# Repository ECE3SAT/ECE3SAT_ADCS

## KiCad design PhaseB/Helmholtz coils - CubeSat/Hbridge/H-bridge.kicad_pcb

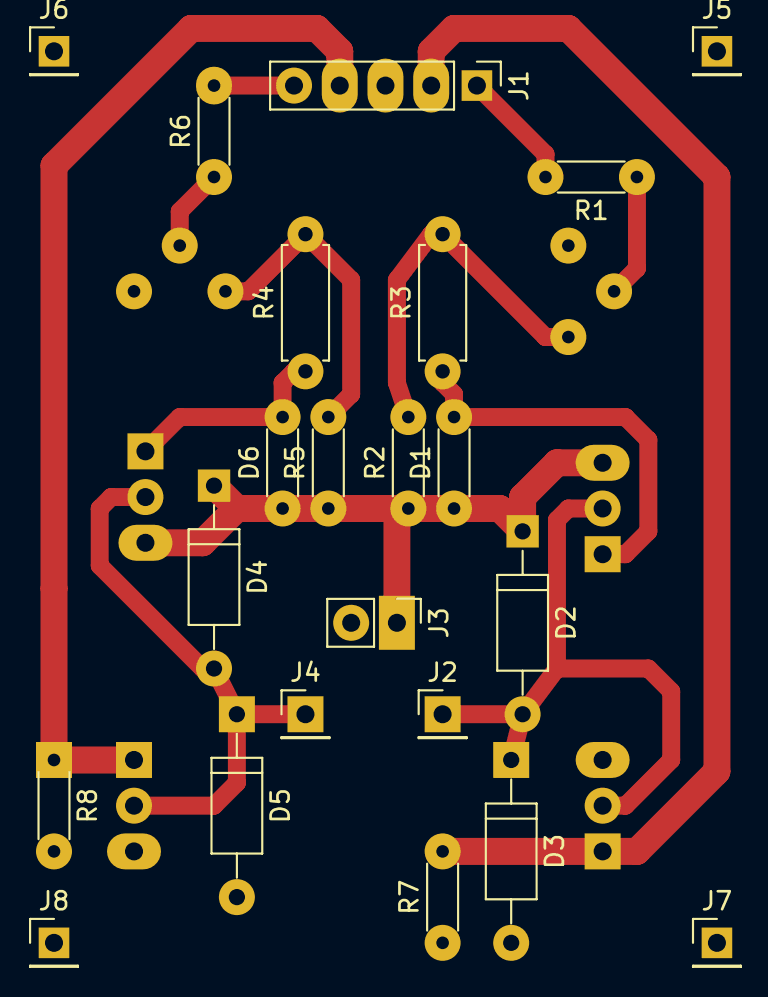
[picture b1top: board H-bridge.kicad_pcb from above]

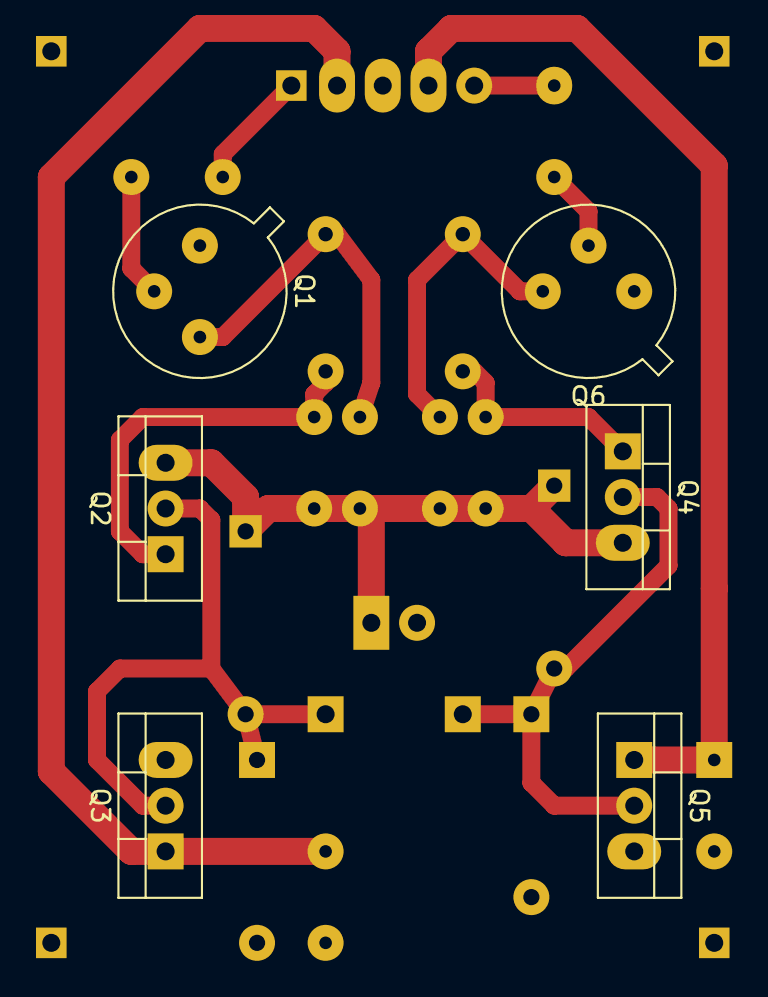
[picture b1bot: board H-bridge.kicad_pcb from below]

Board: 2 copper layers, 28 parts (6 on the bottom side), 14 nets.

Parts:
D1, D6: 10V; R_Axial_DIN0204_L3.6mm_D1.6mm_P5.08mm_Horizontal
D2, D3, D4, D5: 1N4007; D_A-405_P10.16mm_Horizontal
J1: Conn_01x05; Pin_Header_Straight_1x05_Pitch2.54mm
J2, J4, J5, J6, J7, J8: Conn_01x01; Pin_Header_Straight_1x01_Pitch2.54mm
J3: Conn_01x02; Pin_Header_Straight_1x02_Pitch2.54mm
Q1, Q6: BF259; TO-39-3_Window
Q2, Q4: FQP27P06; TO-220-3_Vertical
Q3, Q5: FQP13N10; TO-220-3_Vertical
R1, R6: 1k; R_Axial_DIN0204_L3.6mm_D1.6mm_P5.08mm_Horizontal
R2, R5: 10k; R_Axial_DIN0204_L3.6mm_D1.6mm_P5.08mm_Horizontal
R3, R4: 4k7; R_Axial_DIN0207_L6.3mm_D2.5mm_P7.62mm_Horizontal
R7, R8: 100k; R_Axial_DIN0204_L3.6mm_D1.6mm_P5.08mm_Horizontal

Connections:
GND: D3.2, D5.2, J1.3, J3.2, Q1.1, Q3.3, Q5.3, Q6.1, R7.1, R8.2
N_A: J1.4, Q5.1, R8.1
N_B: J1.2, Q3.1, R7.2
unnamed: D1.2, Q2.1, R3.1
unnamed: D2.2, D3.1, J2.1, Q2.2, Q3.2
unnamed: D4.2, D5.1, J4.1, Q4.2, Q5.2
unnamed: D6.2, Q4.1, R4.1
unnamed: Q1.2, R1.1
unnamed: Q1.3, R2.2, R3.2
unnamed: Q6.2, R6.1
unnamed: Q6.3, R4.2, R5.2
P_A: J1.1, R1.2
P_B: J1.5, R6.2
VDC: D1.1, D2.1, D4.1, D6.1, J3.1, Q2.3, Q4.3, R2.1, R5.1

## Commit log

2017-04-02 Add files via upload
    Wiki pages copy added
2017-04-04 MAJ
    update programme
2017-04-05 Update install
2017-04-11 Add files via upload
    New possibility to change size of the UI
2017-09-19 Update of the project for the begining of 2017
    Deletion of the wiki folder, update of the Simulator code, licence file
2017-09-19 update of the licence
    licence CC-BY-NC
2017-09-19 update of the readme
2018-02-06 PhaseB update
    Simulator code added with the arduino code to test the BDOT
2018-02-06 Python reading of serial
    Trace the magnetorquers graph read from the serial port
2018-02-09 Simulation update
    Last version of the simulator, BDOT needs to be improoved
2018-02-19 Helmoltz + CubeSat ressources added
    All the code and models of the CubeSats and helmoltz environment are added
